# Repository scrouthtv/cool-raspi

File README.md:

# Casing with 40mm fan support for the Raspberry Pi 4 Model B

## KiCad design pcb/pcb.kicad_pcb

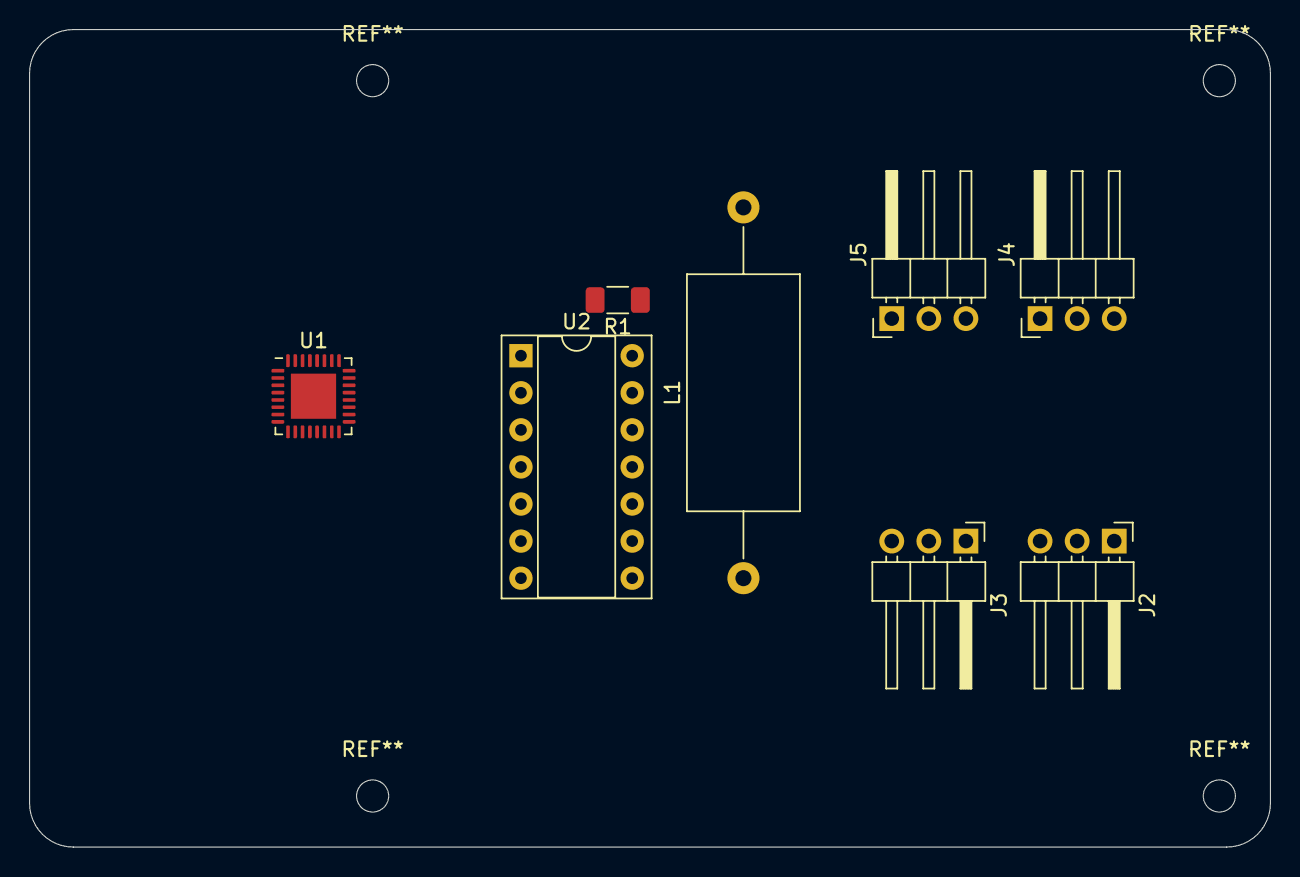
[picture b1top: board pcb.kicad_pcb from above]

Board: 2 copper layers, 85.0 x 56.0 mm, 8 parts (0 on the bottom side), 11 nets, no tracks yet.

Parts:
J2, J3, J4, J5: Conn_01x03; PinHeader_1x03_P2.54mm_Horizontal
L1: L; L_Axial_L16.0mm_D7.5mm_P25.40mm_Horizontal_Fastron_XHBCC
R1: 1R6; R_1206_3216Metric_Pad1.30x1.75mm_HandSolder
U1: ATmega168PB-MU; QFN-32-1EP_5x5mm_P0.5mm_EP3.1x3.1mm
U2: TL497A; DIP-14_W7.62mm_Socket

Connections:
+5V: U1.4, U1.18
+12V: R1.1, U2.14
GND: J2.1, J3.1, J4.1, J5.1, U1.5, U1.20, U1.21, U1.33, U2.4, U2.5, U2.7
INH: U1.1, U2.2
Meas1: J2.3, U1.2
Meas2: J3.3, U1.9
Meas3: J4.3, U1.10
Meas4: J5.3, U1.11
unnamed: L1.1, U2.6, U2.8
unnamed: R1.2, U2.10, U2.13
Vout: J2.2, J3.2, J4.2, J5.2, L1.2

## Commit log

2021-12-21 v1 wip, might remove two fans idk
2021-12-21 added image
2021-12-21 fixed the image
